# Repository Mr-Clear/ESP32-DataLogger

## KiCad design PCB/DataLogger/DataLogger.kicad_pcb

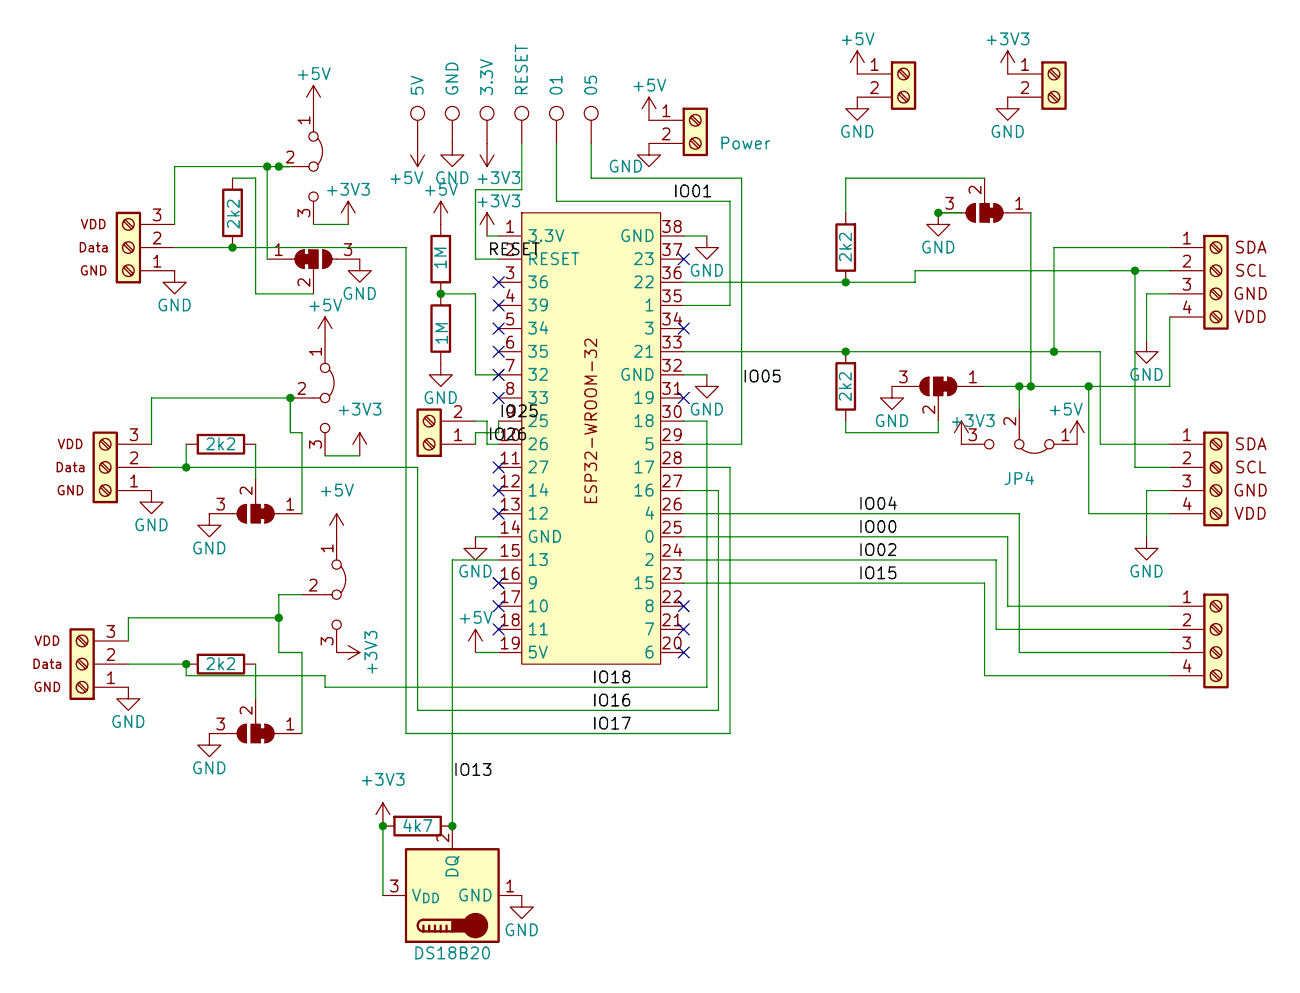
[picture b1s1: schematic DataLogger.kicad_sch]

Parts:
1WI1, 1WI2, 1WI3: 1WI Screw_Terminal_01x03; Screw Terminal 3*2.54 1WI
ExtraGPIO1: Screw_Terminal_01x04; Screw Terminal 4*2.54
ExtraGPIO2: Screw_Terminal_01x; Screw Terminal 2*2.54
I²C1, I²C2: I²C_Screw_Terminal_01x04; Screw Terminal 4*2.54 I²C
J8, J9: Screw_Terminal_01x02; Screw Terminal 2*2.54
JP1, JP2, JP3, JP4: Jumper_3_Bridged12; Jumper
JP5, JP6, JP7, JP8, JP9: SolderJumper_3_Bridged12; SolderJumper-3_P1.3mm_Bridged12_RoundedPad1.0x1.5mm_NumberL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
Power1: Power; Screw Terminal 2*2.54 Power
R1, R2, R3, R9, R10: 2k2; R_Axial_DIN0207_L6.3mm_D2.5mm_P7.62mm_Horizontal
R4: 4k7; R_Axial_DIN0207_L6.3mm_D2.5mm_P7.62mm_Horizontal
R5, R6: 1M; R_Axial_DIN0207_L6.3mm_D2.5mm_P7.62mm_Horizontal
TP1: 5V; TestPoint_THTPad_D1.5mm_Drill0.7mm
TP2: GND; TestPoint_THTPad_D1.5mm_Drill0.7mm
TP3: 3.3V; TestPoint_THTPad_D1.5mm_Drill0.7mm
TP4: RESET; TestPoint_THTPad_D1.5mm_Drill0.7mm
TP5: 01; TestPoint_THTPad_D1.5mm_Drill0.7mm
TP6: 05; TestPoint_THTPad_D1.5mm_Drill0.7mm
U1: ESP32 Board
U2: DS18B20; TO-92_Inline

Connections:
+3V3: J9.1, JP1.3 (B), JP2.3 (B), JP3.3 (B), JP4.3 (B), R4.2, TP3.1, U1.1 (3.3V), U2.3 (V_{DD})
+5V: J8.1, JP1.1 (A), JP2.1 (A), JP3.1 (A), JP4.1 (A), Power1.1 (5V), R5.2, TP1.1, U1.19 (5V)
/IO00: ExtraGPIO1.1, U1.25 (0)
/IO01: TP5.1, U1.35 (1)
/IO02: ExtraGPIO1.2, U1.24 (2)
/IO04: ExtraGPIO1.3, U1.26 (4)
/IO05: TP6.1, U1.29 (5)
/IO13: R4.1, U1.15 (13), U2.2 (DQ)
/IO15: ExtraGPIO1.4, U1.23 (15)
/IO16: 1WI2.2 (Data), R2.2, U1.27 (16)
/IO17: 1WI1.2 (Data), R1.1, U1.28 (17)
/IO18: 1WI3.2 (Data), R3.2, U1.30 (18)
/IO25: ExtraGPIO2.1, U1.9 (25)
/IO26: ExtraGPIO2.2, U1.10 (26)
/RESET: TP4.1, U1.2 (RESET)
GND: 1WI1.1 (GND), 1WI2.1 (GND), 1WI3.1 (GND), I²C1.3 (GND), I²C2.3 (GND), J8.2, J9.2, JP5.3 (B), JP6.3 (B), JP7.3 (B), JP8.3 (B), JP9.3 (B), Power1.2 (GND), R6.1, TP2.1, U1.14 (GND), U1.32 (GND), U1.38 (GND), U2.1 (GND)
unnamed: 1WI1.3 (VDD), JP1.2 (C), JP5.1 (A)
unnamed: 1WI2.3 (VDD), JP2.2 (C), JP6.1 (A)
unnamed: 1WI3.3 (VDD), JP3.2 (C), JP7.1 (A)
unnamed: I²C1.2 (SCL), I²C2.2 (SCL), R9.1, U1.36 (22)
unnamed: I²C1.1 (SDA), I²C2.1 (SDA), R10.2, U1.33 (21)
unnamed: I²C1.4 (VDD), I²C2.4 (VDD), JP4.2 (C), JP8.1 (A), JP9.1 (A)
unnamed: JP5.2 (C), R1.2
unnamed: JP6.2 (C), R2.1
unnamed: JP7.2 (C), R3.1
unnamed: JP8.2 (C), R9.2
unnamed: JP9.2 (C), R10.1

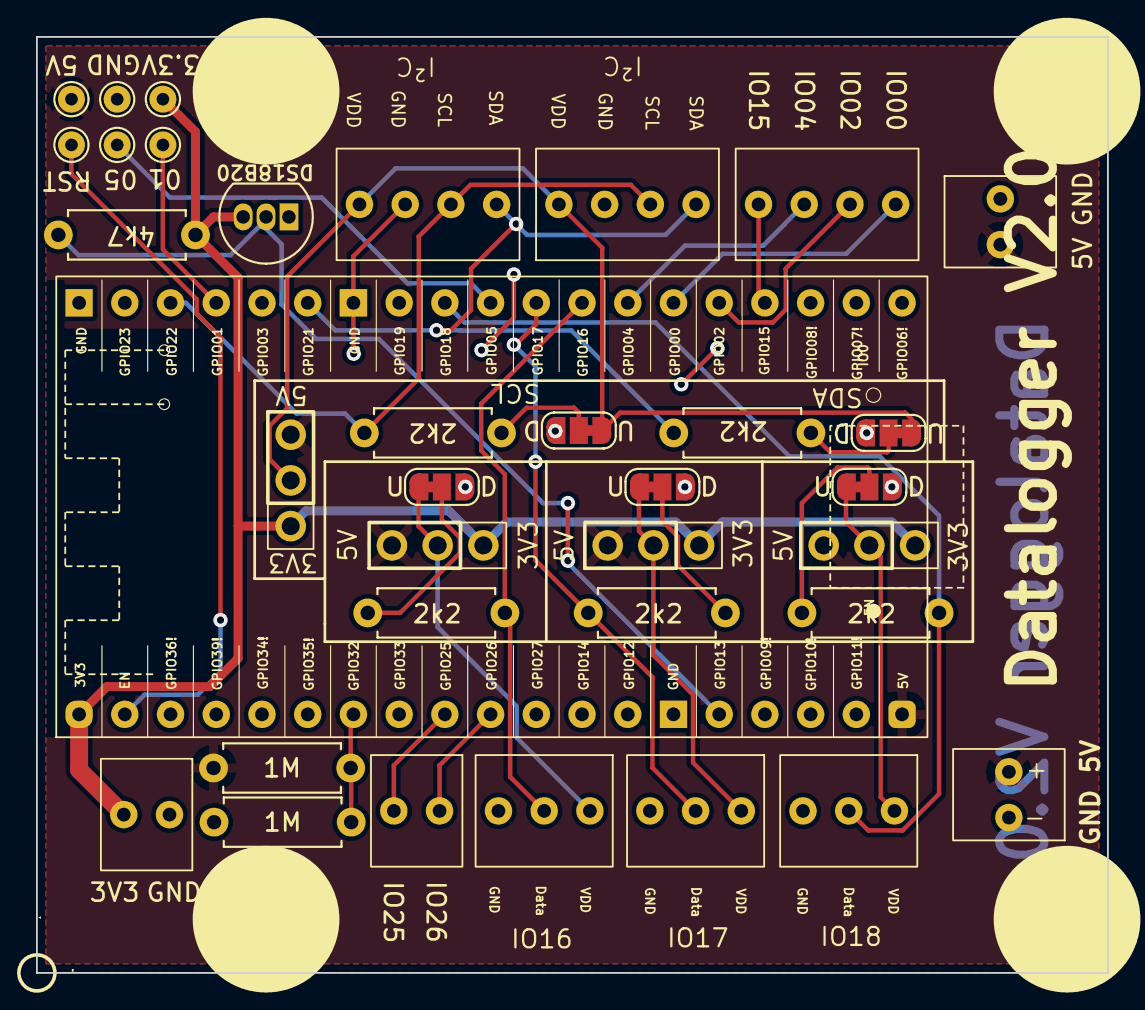
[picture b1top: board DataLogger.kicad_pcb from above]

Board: 2 copper layers, 59.5 x 52.0 mm, 35 parts (0 on the bottom side), 27 nets.

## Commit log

2023-03-24 Read button values
2023-03-24 Document required libraries
2023-03-24 Connect to WIFI and get time
2023-03-25 Push data to www.klierlinge.de
2023-03-25 Wrap drawString
2023-03-26 Run HTTP POST in seperate task
2023-03-30 Handle WiFi in seperate task
2023-03-30 Create Fibers
2023-04-05 Read SHT30 in fiber
2023-04-05 Show heap size
2023-04-06 Hello World!
2023-04-07 Create Tasks and Gui library and move files to there
2023-04-08 Create Queue for inter process communication
2023-04-08 Create QueueTask
2023-04-08 Put TFT code into QueueTask
2023-04-08 Tft class doesn't derive from TFT_eSPI
2023-04-08 Move TftTask into Tft class
2023-04-08 Fix memory leak
2023-04-08 Pass values of SHT30 via Observable
2023-04-08 Hand data to HttpPostTask via Queue
2023-04-08 Handle data from DS18B20 sensors in own Fiber
2023-04-12 Don't post old data
2023-04-12 GPIO interrupt
2023-04-13 Control backlite with buttons
2023-05-13 Handle memory stats in fiber
2023-05-13 Update Wifi status on change
2023-05-13 Add ObervableFilter
2023-05-14 Define text position by col and row
2023-05-18 Read supply voltage in fiber
2023-11-04 Add more functions to queue
2023-11-04 Remove VoidQueue
2023-11-04 Change QueueTask to not remove message from queue when handling failes
2023-11-04 Send timestamp if known
2023-11-04 By default, notify listerner even when the value didn't change
    This is an eval hack but it makes the current use case much simplert
2023-11-04 Create update in increasing interval if upload fails
2023-11-08 Update submodules
2023-11-09 Balkon V1
2023-11-10 Add info images
2023-11-17 Terrasse
2023-11-17 Adopt improvements made in branch Terrasse
2023-11-17 Replace SHT30 with DHT21
2024-02-02 Create PCB
2024-02-02 Ordered Board
2024-02-28 PCB V1.2
2024-02-28 Add submodules
2024-10-06 C++23
2024-10-07 Have each DS18B20 on seperate pin
2024-10-09 Rescan in correct thread
2024-10-09 Add fiber for DHT21 sensor
2024-10-09 Update to PCB layout
2024-10-09 Fix submodules
2024-10-09 Change platform to early access
2024-10-09 Update submodule
2024-10-11 Keller
2024-10-11 Küche
2024-10-12 Remove some library submodules and replace them with PIO lib_deps
2024-10-12 Fix min max of pressure
2025-01-19 Add voltage devider to measure supply voltage
2025-01-25 Bedroom
2025-01-25 Office
2025-01-26 Bad: Replace DHT21 with DHT20
